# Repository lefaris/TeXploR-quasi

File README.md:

# TeXploR-quasi

This repository contains the system design documentation and quasistatic simulation for **TeXploR2** (Tensegrity eXploratory Robot 2), a curved-link tensegrity robot capable of dynamic rolling locomotion through internal mass shifting. This work represents a significant advancement over the [original TeXploR](https://github.com/lefaris/TeXploR-geometric).  This repo is supplemental for **System Design of Tensegrity Robot Exhibiting Non-Intuitive Behavior** accepted to IEEE ICRA 2026.

---

*TeXploR2 (left, black) compared to the original TeXploR (right, red). TeXploR2 is completely redesigned for smoother dynamic movement regardless of shifting mass orientation (e.g., hanging upside down). The prototype is also significantly larger for additional central payload capabilities.*

## Overview

TeXploR2 is a curved-link tensegrity robot that achieves efficient rolling while maintaining stability through discontinuities present at arc endpoints. Unlike traditional straight-link tensegrity robots that contain slower toppling/walking locomotion gaits, TeXploR2's spherical-like design enables rolling.

### Key Contributions

This work showcases the system design for the TeXploR2 prototype. We also introduce non-intuitive state switching behavior that enables state transitions without requiring the shifting mass to reach arc endpoints. This enables faster state jumping and trajectory control.

- **Updated System Design**: More robust prototype capable of real-time tetherless locomotion
- **Non-Intuitive Control**: Efficient state jumping achievable along boundary lines
- **Shock Absorption**: Compliant tensegrity structure withstands impacts
- **Modular Modeling Framework and Design**: Scalable to additional curved links for finer control

---
## Demos

### Shifting Mass

### Rolling Locomotion

### Impact Test

---

## Repository Structure

```
TeXploR-quasi/
├── quasistatic_modeling/   # MATLAB quasistatic simulation code
│   └── visualization/      # Simulation visualization
├── experiments/            # Motion capture data and test scripts
├── design_files/           # TeXploR2 design files
│   ├── CAD/                # Fusion files
│   └── PCB/                # KiCAD files
└── figures/                # Demo figures/videos
```

---

## Getting Started

### Prerequisites

- MATLAB R2020b or later
- Optional: Python 3.x (for hardware integration)

### Installation

1. **Clone the repository**
   ```bash
   git clone https://github.com/lefaris/TeXploR-quasi.git
   cd TeXploR-quasi
   ```

2. **Set up MATLAB path**
   ```matlab
   addpath(genpath('quasistatic_modeling'))
   ```

3. **Run quasistatic simulation**
   ```matlab
   cd quasistatic_modeling
   run('TExploRStaticsDerivationsQuasi3(0, 90)')
   ```

---

## System Design

### Mechanical Properties

| Component | Specification |
|-----------|--------------|
| **Arc Diameter** | 585mm (vs. 403mm TeXploR v1) |
| **Arc Width** | 98mm (vs. 83mm TeXploR v1) |
| **Arc Mass** | ~1,300g each |
| **Shifting Mass** | 1,150g each |
| **Mass Ratio** | 0.88:1 (shifting:arc) |
| **Material** | Onyx (Markforged) |

### Electronics

- **Controller**: Raspberry Pi Zero 2W
- **Motors**: Dual-shaft NEMA23 bipolar stepper motors (200 steps/rev)
- **Motor Drivers**: TB67S128FTG high-current carriers
- **Sensors**: 9-axis IMU (I2C)
- **Power**: 11.4V 1.5Ah LiPo battery
- **Control**: Open-loop with SSH remote control
- **Board**: Custom PCB

### Motor Carriage Design

- **T-track latching**: For precise alignment
- **8 v-groove bearings**: (4 horizontal, 4 vertical) to prevent rotation and maintain grip
- **6 ball bearings**: For smooth rolling along arc curvature
- **Herringbone gear teeth**: For smooth power transmission at high loads

### Arc Design

- **Dual internal gear racks**: Parallel along inner curvature
- **Matching Pinion gears**: Driven by dual-shaft NEMA23 motor
- **Symmetric mass distribution**: Minimizes model discrepancies
- **98mm width**: Minimum for NEMA23 integration

---

## Citation

If you use this work in your research, please cite both papers:

### TeXploR2 (ICRA 2026)

```bibtex
@inproceedings{texplor2_2026,
  title={System Design of Tensegrity Robot Exhibiting Non-Intuitive Behavior},
  author={Ervin, Lauren and Bezawada, Harish and Vikas, Vishesh},
  booktitle={2026 IEEE International Conference on Robotics and Automation (ICRA)},
  year={2026},
  organization={IEEE}
}
```
**arXiv preprint:** [arXiv](https://arxiv.org) (Coming Soon)

### TeXploR Geometric Modeling (IEEE RA-L 2024)

```bibtex
@article{texplor_2024,
  title={Geometric Static Modeling Framework for Piecewise-Continuous Curved-Link Multi Point-of-Contact Tensegrity Robots},
  author={Ervin, Lauren and Vikas, Vishesh},
  journal={IEEE Robotics and Automation Letters},
  year={2024},
  volume={9},
  number={12},
  pages={11066-11073},
  doi={10.1109/LRA.2024.3486199}
}
```

---

## Updates

- **January 2026:** Paper accepted to IEEE ICRA 2026
- **September 2025:** Version 2 of [TeXploR robot design](https://github.com/lefaris/TeXploR-geometric) submitted to IEEE ICRA 2026

---

## License

This project is released for academic and research purposes.

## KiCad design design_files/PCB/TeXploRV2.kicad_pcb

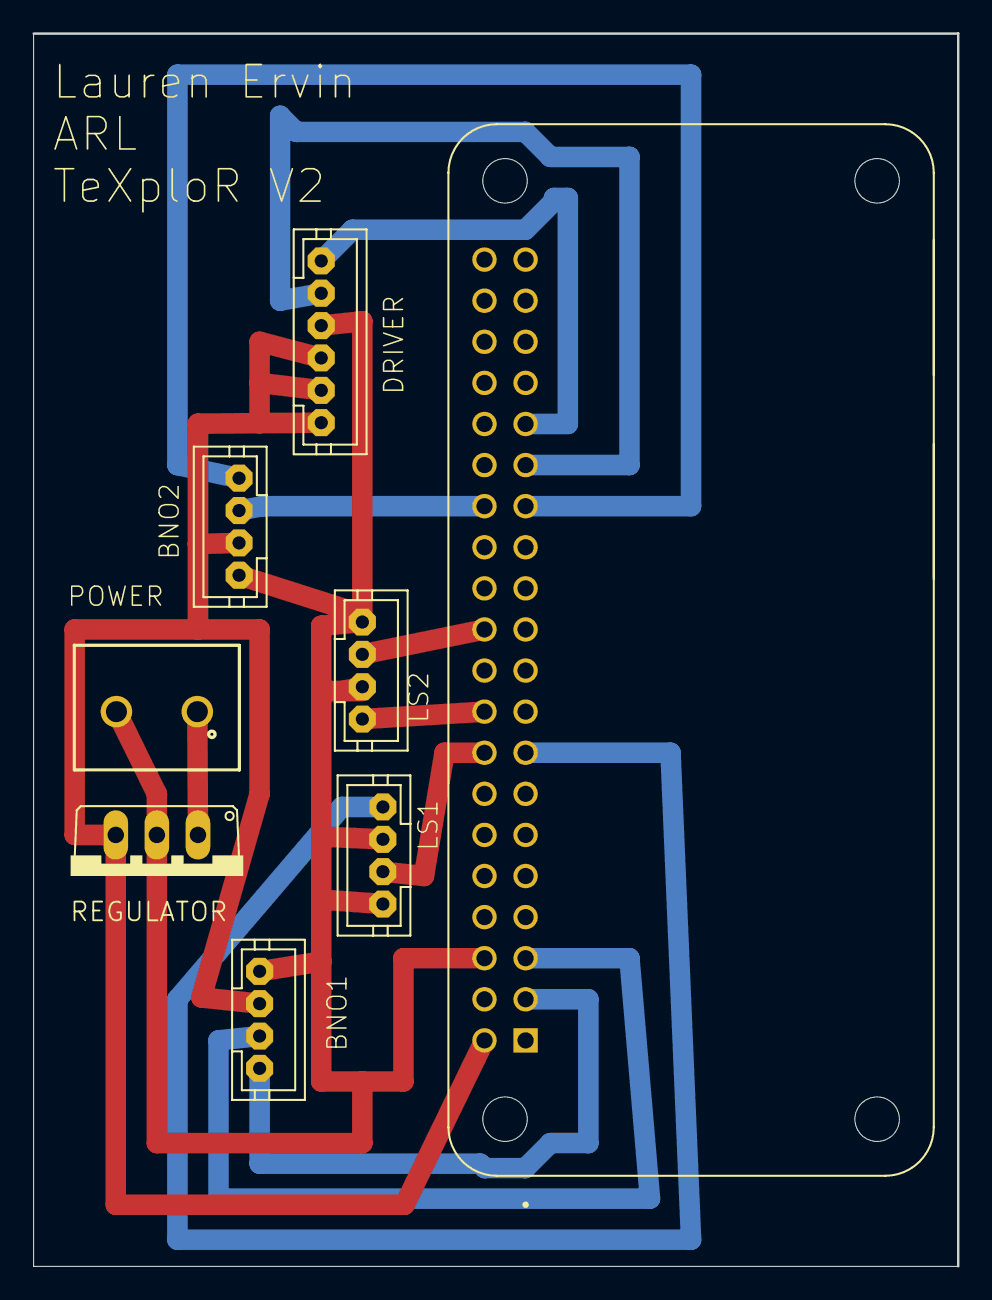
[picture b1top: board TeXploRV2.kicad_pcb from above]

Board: 2 copper layers, 57.1 x 76.2 mm, 8 parts (0 on the bottom side), 13 nets.

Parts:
BNO1, BNO2: JST-PH4
DRIVER: JST-PH6
LS1, LS2: JST-PH4
POWER: 691137710002; 691137710002_16177944
REGULATOR: 7805TV; TO220V_262
U1: RASPBERRY_PI_ZERO_2_W; MODULE_RASPBERRY_PI_ZERO_2_W

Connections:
5V: BNO1.3, BNO2.3, DRIVER.1, DRIVER.2, DRIVER.3, REGULATOR.3, U1.2
DIR: DRIVER.5, U1.29
GND: BNO1.4, BNO2.4, DRIVER.4, LS1.2, LS1.4, LS2.2, LS2.4, POWER.2, REGULATOR.2, U1.6
GPIO22: LS1.1, U1.15
GPIO23: LS1.3, U1.16
GPIO24: LS2.1, U1.18
GPIO25: LS2.3, U1.22
SCL1: BNO1.2, U1.5
SCL2: BNO2.2, U1.28
SDA1: BNO1.1, U1.3
SDA2: BNO2.1, U1.27
STEP: DRIVER.6, U1.31
VIN: POWER.1, REGULATOR.1

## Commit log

2026-02-11 Added PCB and CAD design files
2026-02-12 figure renaming
    Updated image file extensions from .png to .PNG for consistency.
2026-03-01 IMU collection
2026-03-04 Vicon curved members
2026-03-05 Adding accel data
2026-04-22 updated accelerometer graph
